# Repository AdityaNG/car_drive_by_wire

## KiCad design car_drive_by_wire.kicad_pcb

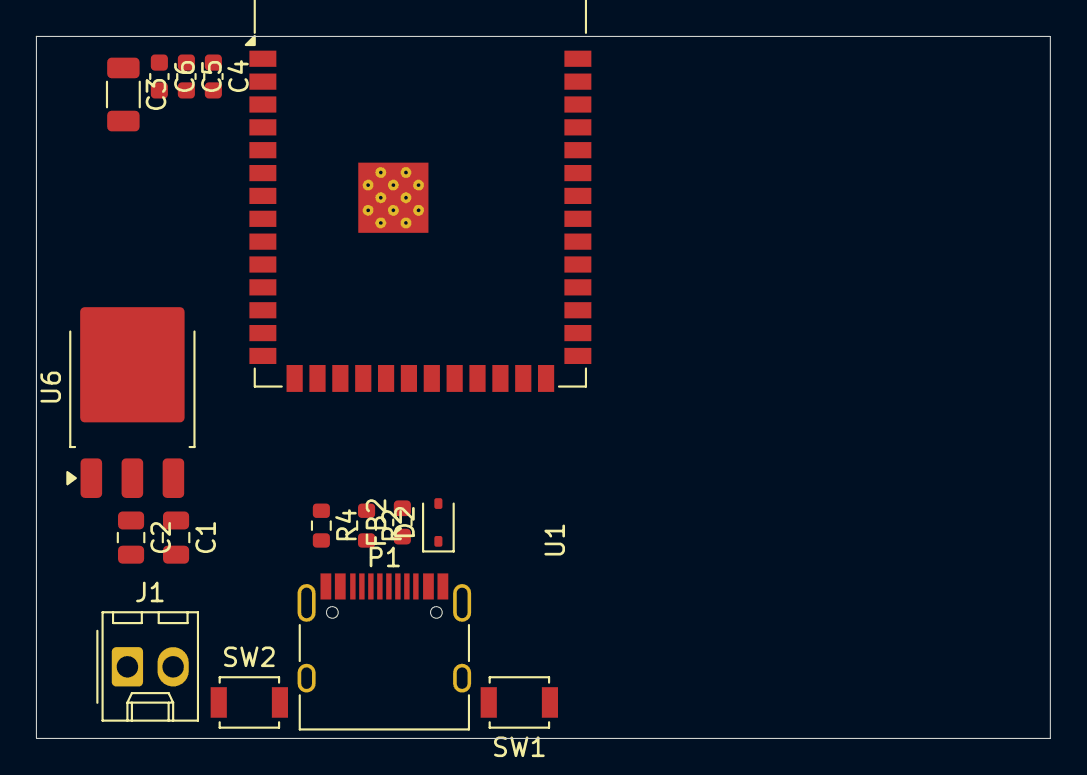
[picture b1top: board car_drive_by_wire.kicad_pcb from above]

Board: 2 copper layers, 56.3 x 39.0 mm, 16 parts (0 on the bottom side), 11 nets, no tracks yet.

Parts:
C1, C2: C; C_0805_2012Metric
C3: C10uF; C_1206_3216Metric
C4, C5, C6: C100nF; C_0603_1608Metric
D2: 1N5819WS; D_SOD-323
FB2: 500mA?; L_0603_1608Metric
J1: POW; Molex_KK-254_AE-6410-02A_1x02_P2.54mm_Vertical
P1: USB_C_Receptacle_USB2.0; USB_C_Receptacle_HRO_TYPE-C-31-M-12
R2, R4: 5.1k; R_0603_1608Metric
SW1, SW2: SW_Push; SW_SPST_B3U-1000P
U1: ESP32-S3-WROOM-1
U6: LM1117DT-3.3; TO-252-3_TabPin2

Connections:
3V3: C2.1, C3.2, C4.2, C5.2, C6.2, U1.2 (3V3), U6.2 (VO)
5V: C1.1, FB2.2, J1.2, U6.3 (VI)
/CC1_2: P1.A5 (CC1), R2.1
/CC2_2: P1.B5 (CC2), R4.1
/VBUS2: D2.2 (A), P1.A4 (VBUS), P1.A9 (VBUS), P1.B4 (VBUS), P1.B9 (VBUS)
ESP_EN: SW2.1, U1.3 (EN)
GND: C1.2, C2.2, C3.1, C4.1, C5.1, C6.1, J1.1, P1.A1 (GND), P1.A12 (GND), P1.B1 (GND), P1.B12 (GND), P1.S1 (SHIELD), R2.2, R4.2, SW1.2, SW2.2, U1.1 (GND), U1.40 (GND), U1.41 (GND), U6.1 (GND)
unnamed: D2.1 (K), FB2.1
SW_BOOT: SW1.1, U1.27 (IO0)
USB_DM: P1.A7 (D-), P1.B7 (D-), U1.13 (USB_D-)
USB_DP: P1.A6 (D+), P1.B6 (D+), U1.14 (USB_D+)

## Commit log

2025-11-10 car_drive_by_wire
2025-11-10 minor change
2025-11-10 Minor change again
2025-11-10 test from windows
